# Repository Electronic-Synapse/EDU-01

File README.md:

# EDU-01 — Analog Drone Synth (educational kit)

Three saw-core VCOs mixed, soft-clipped and run through a resonant
low-pass filter. Everything on a single +5 V USB-C supply, built only
from common **through-hole** parts — meant to be built on a real PCB,
probed at every stage, and used to teach analog synth fundamentals.

```
USB-C 6-pin breakout ─ F1 polyfuse ─ L1 ferrite ─ +5V
                                        │
                              R2/R3 divider + U3C buffer = VREF (2.5 V)
                                        │
   TUNE_1 LEVEL_1   OSC1 ─┐             │
   TUNE_2 LEVEL_2   OSC2 ─┼─ mixer U2C ─ clip U2D ─ Sallen-Key U3A ─ buffer U3B ─ MASTER_LEVEL ─ J2 3.5 mm
   TUNE_3 LEVEL_3   OSC3 ─┘                LED pair       CUTOFF1    RES1           A10k
                                        D2/D3 via R32
                                        to VREF
```

## Key specs

| Spec | Value |
| --- | --- |
| Supply | USB-C VBUS 5 V via 6-pin 2.54 mm breakout (polyfuse + ferrite) |
| Virtual ground | VREF = 2.5 V (R2/R3 divider, buffered by U3C) |
| Oscillators | 3× op-amp saw core (integrator + comparator + BC547 cap reset) |
| Osc range | ~0–1.5 kHz (4.7 k Rin), parks at 0 Hz at the low end of TUNE |
| Mixer | Inverting summer, unity gain per osc (10 k/10 k) |
| Clip | Shunt LED clipper on U2D out: anti-parallel red LEDs + 220 Ω to VREF |
| Filter | 2-pole Sallen-Key LP, ~72 Hz–7.2 kHz cutoff (dual-gang 100k + 1 k min), RES to self-oscillation |
| RES limit | Anti-parallel yellow LEDs across RES1: oscillation settles ~±2 V clean sine |
| Output | AC-coupled 10 µF → A10k master level → 1 k series R to tip+ring, sleeve = GND |
| Test points | TP1 +5V, TP2 VREF, TP3–5 SAW1–3, TP6 MIX, TP7 CLIP, TP8 OUT, TP9 GND |

## Controls (9 pots)

- **TUNE_1/2/3** — B10k, oscillator pitch (current into the integrator)
- **LEVEL_1/2/3** — B10k, per-osc level into the mixer
- **CUTOFF1** — dual-gang 100k, tracks both filter sections
- **RES1** — B22k, filter feedback; self-oscillation over the top half
  (yellow LEDs light when the filter sings)
- **MASTER_LEVEL1** — A10k (audio taper), output volume after the DC-block cap

## Design notes

- **Op-amps**: 3× MCP6004-I/P (DIP-14), chosen because TL07x cannot run on
  a single 5 V rail (its input common-mode range doesn't include ground).
  MCP6004 is rail-to-rail I/O and cheap/common.
- **Saw core**: tune pot feeds current through R_in (4.7 k) into the
  integrator summing node; the comparator trips at ~0.9 V (R5/R6 divider)
  and pulses the BC547 base, discharging the integrator cap (E→SAW,
  C→summation).
- **Clip**: U2D is a ×2 inverting stage (R24/R23); its output feeds an
  anti-parallel red LED pair through R32 (220 Ω) to VREF. When the signal
  exceeds ~±Vf (~1.9 V red) around VREF, the LEDs squash the peak and
  visibly blink — a shunt clipper referenced to the virtual ground,
  *not* to GND.
- **Filter Q**: RES1 (B22k) varies feedback against R28 (4.7 k) at
  U3A −in: gain range ≈ 1→5.7, so Q crosses self-oscillation at ~40 %
  of travel — the top of the pot is an oscillator whose pitch follows
  CUTOFF1.
- **RES limiter**: an anti-parallel yellow LED pair sits in parallel
  with RES1's feedback path. Below ~±2 V they are transparent; past the
  self-oscillation threshold they collapse the feedback gain, so the
  loop settles into a clean ~±2 V sine instead of slamming the op-amp
  rails. Yellow lit = filter oscillating, red lit = signal clipping —
  classic amplitude stabilization, and a nice live readout.
- **LED choice**: only low-Vf colors work here — the op-amp can only
  swing ~±2 V around VREF, so blue/white/true-green (~3 V) would never
  conduct. Red for the clipper (lowest threshold), yellow for RES.
- All resistors 1 %, all caps TH ceramic (100 n/22 n) or electrolytic
  (1 µ/10 µ/100 µ).

## Files

```
kicad/edu-01.kicad_pro   project
kicad/edu-01.kicad_sch   schematic
kicad/edu-01.kicad_pcb   board layout
```

## BOM (core parts)

| Qty | Part |
| --- | --- |
| 3 | MCP6004-I/P (DIP-14) |
| 3 | BC547 (TO-92) |
| 5 | LED (1 × power, 2 × red clip pair, 2 × yellow RES pair) |
| 6 | B10k 9 mm vertical pot (Alpha RD901F-style) |
| 1 | A10k 9 mm vertical pot (master level) |
| 1 | dual-gang 100k pot (RD902F-style) |
| 1 | B22k 9 mm pot |
| 31 | resistors 1 % (0.25 W, axial): 10×10k, 7×4.7k, 3×47k, 3×1M, 4×1k, 1×20k, 1×100k, 1×1.5k, 1×220 |
| 16 | ceramic + electrolytic caps (TH) |
| 1 | USB-C 6-pin 2.54 mm breakout |
| 1 | polyfuse 500 mA, ferrite bead, SJ1-3533NG 3.5 mm jack |

## Build notes

- J1 pinout used: **1 = VBUS, 2 = GND**; pins 3–6 are NC on the board.
- **CC resistors**: for a USB-C host/charger to deliver power, both
  CC1 and CC2 must each see **5.1 kΩ to GND** (Rd). Check your
  breakout's silkscreen — many 6-pin boards already have them fitted;
  if not, add one 5.1 kΩ from each CC pin to GND. Never share a single
  resistor between CC1/CC2, and don't duplicate on-board if the
  breakout has them (parallel → ~2.55 kΩ → source refuses power).
- Transistor pinout: **BC547 is C-B-E** — check the silkscreen before
  soldering.
- U3D is a spare op-amp wired as a VREF follower (keep it populated).
- Probe order for a first smoke test: TP1 (+5 V) → TP2 (VREF ≈ 2.5 V) →
  TP3–5 (saws) → TP6 (mix) → TP7 (clip) → TP8 (out).

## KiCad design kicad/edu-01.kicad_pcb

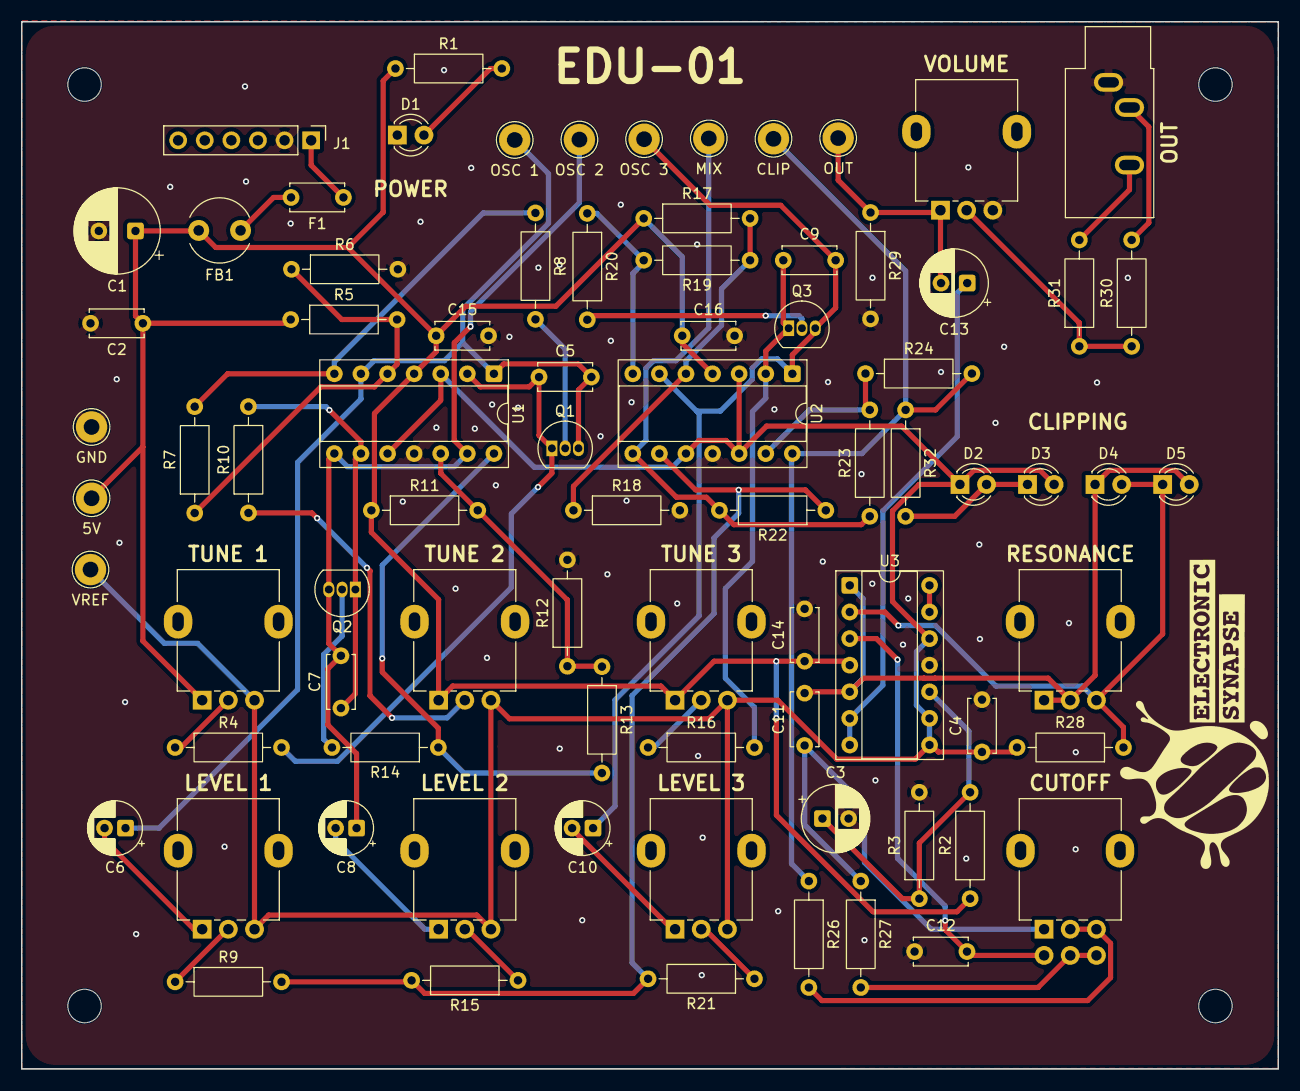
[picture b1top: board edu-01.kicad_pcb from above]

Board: 2 copper layers, 120.0 x 100.0 mm, 80 parts (0 on the bottom side), 48 nets.

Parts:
5V: +5V; TestPoint_THTPad_D3.0mm_Drill1.5mm
C1: 100uF; CP_Radial_D8.0mm_P3.50mm
C2, C4, C14, C15, C16: 100n; C_Disc_D5.0mm_W2.5mm_P5.00mm
C3, C13: 10uF; CP_Radial_D6.3mm_P2.50mm
C5, C7, C9: 220n; C_Disc_D5.0mm_W2.5mm_P5.00mm
C6, C8, C10: 1uF; CP_Radial_D5.0mm_P2.00mm
C11, C12: 22n; C_Disc_D5.0mm_W2.5mm_P5.00mm
CLIP: CLIP; TestPoint_THTPad_D3.0mm_Drill1.5mm
CUTOFF: 100K; Potentiometer_Alpha_RD902F-40-00D_Dual_Vertical
D1: PWR; LED_D3.0mm
D2, D3: RED LED; LED_D3.0mm
D4, D5: YELLOW LED; LED_D3.0mm
F1: 500mA; C_Disc_D5.0mm_W2.5mm_P5.00mm
FB1: FerriteBead; L_Radial_D6.0mm_P4.00mm
GND: GND; TestPoint_THTPad_D3.0mm_Drill1.5mm
J1: USB-C breakout; PinHeader_1x06_P2.54mm_Vertical
LEVEL 1, LEVEL 2, LEVEL 3: B10k; Potentiometer_Alpha_RD901F-40-00D_Single_Vertical
MIX: MIX; TestPoint_THTPad_D3.0mm_Drill1.5mm
OSC 1: SAW1; TestPoint_THTPad_D3.0mm_Drill1.5mm
OSC 2: SAW2; TestPoint_THTPad_D3.0mm_Drill1.5mm
OSC 3: SAW3; TestPoint_THTPad_D3.0mm_Drill1.5mm
OUT: OUT; TestPoint_THTPad_D3.0mm_Drill1.5mm
OUT#2: 3.5mm OUT; Jack_3.5mm_CUI_SJ1-3533NG_Horizontal
Q1, Q2, Q3: BC547; TO-92_Inline
R1: 1.5k; R_Axial_DIN0207_L6.3mm_D2.5mm_P10.16mm_Horizontal
R2, R3, R6, R12, R18, R23: 10k; R_Axial_DIN0207_L6.3mm_D2.5mm_P10.16mm_Horizontal
R4, R8, R10, R14, R16, R20, R28: 4K7; R_Axial_DIN0207_L6.3mm_D2.5mm_P10.16mm_Horizontal
R5, R11, R17: 47k; R_Axial_DIN0207_L6.3mm_D2.5mm_P10.16mm_Horizontal
R7, R13, R19: 1M; R_Axial_DIN0207_L6.3mm_D2.5mm_P10.16mm_Horizontal
R9, R15, R21, R22: 10K; R_Axial_DIN0207_L6.3mm_D2.5mm_P10.16mm_Horizontal
R24: 20k; R_Axial_DIN0207_L6.3mm_D2.5mm_P10.16mm_Horizontal
R26, R27, R30, R31: 1k; R_Axial_DIN0207_L6.3mm_D2.5mm_P10.16mm_Horizontal
R29: 100k; R_Axial_DIN0207_L6.3mm_D2.5mm_P10.16mm_Horizontal
R32: 220; R_Axial_DIN0207_L6.3mm_D2.5mm_P10.16mm_Horizontal
RESONANCE: B22k; Potentiometer_Alpha_RD901F-40-00D_Single_Vertical
TUNE 1, TUNE 2, TUNE 3: B10k; Potentiometer_Alpha_RD901F-40-00D_Single_Vertical
U1, U2, U3: MCP6004; DIP-14_W7.62mm_Socket
VOLUME: A10K; Potentiometer_Alpha_RD901F-40-00D_Single_Vertical
VREF: VREF; TestPoint_THTPad_D3.0mm_Drill1.5mm

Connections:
+5V: 5V.1 (1_1), C1.1, C2.1, C14.1, C15.1, C16.1, FB1.2, R1.1, R2.1, R5.1, R11.1, R17.1, TUNE 1.1, TUNE 2.1, TUNE 3.1, U1.4 (V+), U2.4 (V+), U3.4 (V+)
/VBUS: F1.1, J1.1
/VREF: C4.1, D2.1 (K), D3.2 (A), LEVEL 1.3, LEVEL 2.3, LEVEL 3.3, R28.2, TUNE 1.3, TUNE 2.3, TUNE 3.3, U1.3 (+), U1.10 (+), U2.3 (+), U2.10 (+), U2.12 (+), U3.8, U3.9 (-), U3.12 (+), VREF.1 (1_1)
GND: C1.2, C2.2, C3.2, C4.2, C12.1, C14.2, C15.2, C16.2, D1.1 (K), GND.1 (1_1), J1.2, OUT#2.S, R3.2, R6.2, R12.2, R18.2, R29.2, U1.11 (V-), U2.11 (V-), U3.11 (V-), VOLUME.3
unnamed: C6.2, LEVEL 1.1
unnamed: C8.2, LEVEL 2.1
unnamed: C10.2, LEVEL 3.1
unnamed: C11.1, CUTOFF.1, R27.1
unnamed: C13.2, OUT.1 (1_1), R29.1, VOLUME.1
unnamed: CUTOFF.2, CUTOFF.3, R26.2
unnamed: CUTOFF.5, CUTOFF.6, R27.2
unnamed: D1.2 (A), R1.2
unnamed: D2.2 (A), D3.1 (K), R32.2
unnamed: D4.2 (A), D5.1 (K), R28.1, RESONANCE.3, U3.2 (-)
unnamed: C11.2, D4.1 (K), D5.2 (A), RESONANCE.1, RESONANCE.2, U3.1, U3.5 (+)
unnamed: F1.2, FB1.1
unnamed: OUT#2.R, R31.2
unnamed: OUT#2.T, R30.2
unnamed: LEVEL 1.2, R9.1
unnamed: LEVEL 2.2, R15.1
unnamed: LEVEL 3.2, R21.1
unnamed: R30.1, R31.1, VOLUME.2
unnamed: Q1.2 (B), R8.2
unnamed: C5.1, Q1.1 (C), R4.2, U1.2 (-)
unnamed: C5.2, C6.1, OSC 1.1 (1_1), Q1.3 (E), U1.1, U1.6 (-)
unnamed: Q2.2 (B), R14.2
unnamed: C7.1, Q2.1 (C), R10.2, U1.9 (-)
unnamed: C7.2, C8.1, OSC 2.1 (1_1), Q2.3 (E), U1.8, U1.13 (-)
unnamed: Q3.2 (B), R20.2
unnamed: C9.1, Q3.1 (C), R16.2, U2.2 (-)
unnamed: C9.2, C10.1, OSC 3.1 (1_1), Q3.3 (E), U2.1, U2.6 (-)
unnamed: R4.1, TUNE 1.2
unnamed: R7.2, R8.1, U1.7
unnamed: R10.1, TUNE 2.2
unnamed: R13.2, R14.1, U1.14
unnamed: R16.1, TUNE 3.2
unnamed: R19.2, R20.1, U2.7
unnamed: MIX.1 (1_1), R22.2, R23.1, U2.8
unnamed: CLIP.1 (1_1), R24.2, R26.1, R32.1, U2.14
unnamed: R5.2, R6.1, R7.1, U1.5 (+)
unnamed: R11.2, R12.1, R13.1, U1.12 (+)
unnamed: R17.2, R18.1, R19.1, U2.5 (+)
unnamed: R9.2, R15.2, R21.2, R22.1, U2.9 (-)
unnamed: R23.2, R24.1, U2.13 (-)
unnamed: C12.2, CUTOFF.4, U3.3 (+)
unnamed: C13.1, U3.6 (-), U3.7
unnamed: C3.1, R2.2, R3.1, U3.10 (+)
unnamed: U3.13 (-), U3.14

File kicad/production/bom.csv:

Designator,Footprint,Quantity,Value,LCSC Part #
5V,TestPoint_THTPad_D3.0mm_Drill1.5mm,1,+5V,
C1,CP_Radial_D8.0mm_P3.50mm,1,100uF,
"C10, C6, C8",CP_Radial_D5.0mm_P2.00mm,3,1uF,
"C11, C12",C_Disc_D5.0mm_W2.5mm_P5.00mm,2,22n,
"C13, C3",CP_Radial_D6.3mm_P2.50mm,2,10uF,
"C14, C15, C16, C2, C4",C_Disc_D5.0mm_W2.5mm_P5.00mm,5,100n,
"C5, C7, C9",C_Disc_D5.0mm_W2.5mm_P5.00mm,3,220n,
CLIP,TestPoint_THTPad_D3.0mm_Drill1.5mm,1,CLIP,
CUTOFF,Potentiometer_Alpha_RD902F-40-00D_Dual_Vertical,1,100K,
D1,LED_D3.0mm,1,PWR,
"D2, D3",LED_D3.0mm,2,RED LED,
"D4, D5",LED_D3.0mm,2,YELLOW LED,
F1,C_Disc_D5.0mm_W2.5mm_P5.00mm,1,500mA,
FB1,L_Radial_D6.0mm_P4.00mm,1,FerriteBead,
GND,TestPoint_THTPad_D3.0mm_Drill1.5mm,1,GND,
J1,PinHeader_1x06_P2.54mm_Vertical,1,USB-C breakout,
"LEVEL 1, LEVEL 2, LEVEL 3, TUNE 1, TUNE 2, TUNE 3",Potentiometer_Alpha_RD901F-40-00D_Single_Vertical,6,B10k,
MIX,TestPoint_THTPad_D3.0mm_Drill1.5mm,1,MIX,
OSC 1,TestPoint_THTPad_D3.0mm_Drill1.5mm,1,SAW1,
OSC 2,TestPoint_THTPad_D3.0mm_Drill1.5mm,1,SAW2,
OSC 3,TestPoint_THTPad_D3.0mm_Drill1.5mm,1,SAW3,
OUT_2,TestPoint_THTPad_D3.0mm_Drill1.5mm,1,OUT,
OUT,Jack_3.5mm_CUI_SJ1-3533NG_Horizontal,1,3.5mm OUT,
"Q1, Q2, Q3",TO-92_Inline,3,BC547,
R1,R_Axial_DIN0207_L6.3mm_D2.5mm_P10.16mm_Horizontal,1,1.5k,
"R10, R14, R16, R20, R28, R4, R8",R_Axial_DIN0207_L6.3mm_D2.5mm_P10.16mm_Horizontal,7,4K7,
"R11, R17, R5",R_Axial_DIN0207_L6.3mm_D2.5mm_P10.16mm_Horizontal,3,47k,
"R12, R15, R18, R2, R21, R22, R23, R3, R6, R9",R_Axial_DIN0207_L6.3mm_D2.5mm_P10.16mm_Horizontal,10,10k,
"R13, R19, R7",R_Axial_DIN0207_L6.3mm_D2.5mm_P10.16mm_Horizontal,3,1M,
R24,R_Axial_DIN0207_L6.3mm_D2.5mm_P10.16mm_Horizontal,1,20k,
"R26, R27, R30, R31",R_Axial_DIN0207_L6.3mm_D2.5mm_P10.16mm_Horizontal,4,1k,
R29,R_Axial_DIN0207_L6.3mm_D2.5mm_P10.16mm_Horizontal,1,100k,
R32,R_Axial_DIN0207_L6.3mm_D2.5mm_P10.16mm_Horizontal,1,220,
RESONANCE,Potentiometer_Alpha_RD901F-40-00D_Single_Vertical,1,B22k,
"U1, U2, U3",DIP-14_W7.62mm_Socket,3,MCP6004,
VOLUME,Potentiometer_Alpha_RD901F-40-00D_Single_Vertical,1,A10K,
VREF,TestPoint_THTPad_D3.0mm_Drill1.5mm,1,VREF,
